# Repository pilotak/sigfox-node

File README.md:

# Sigfox temperature & humidity sensor

Outdoor battery powered temperature & humidity IOT sensor with integrated Sigfox transceiver and battery state monitor.

All data are sent to Sigfox backend, in order to save them to ie.: InfluxDB you can use  [Sigfox to InfluxDB convertor](https://github.com/pilotak/docker-sigfox-influxdb).

For more information please visit [wiki](./wiki)

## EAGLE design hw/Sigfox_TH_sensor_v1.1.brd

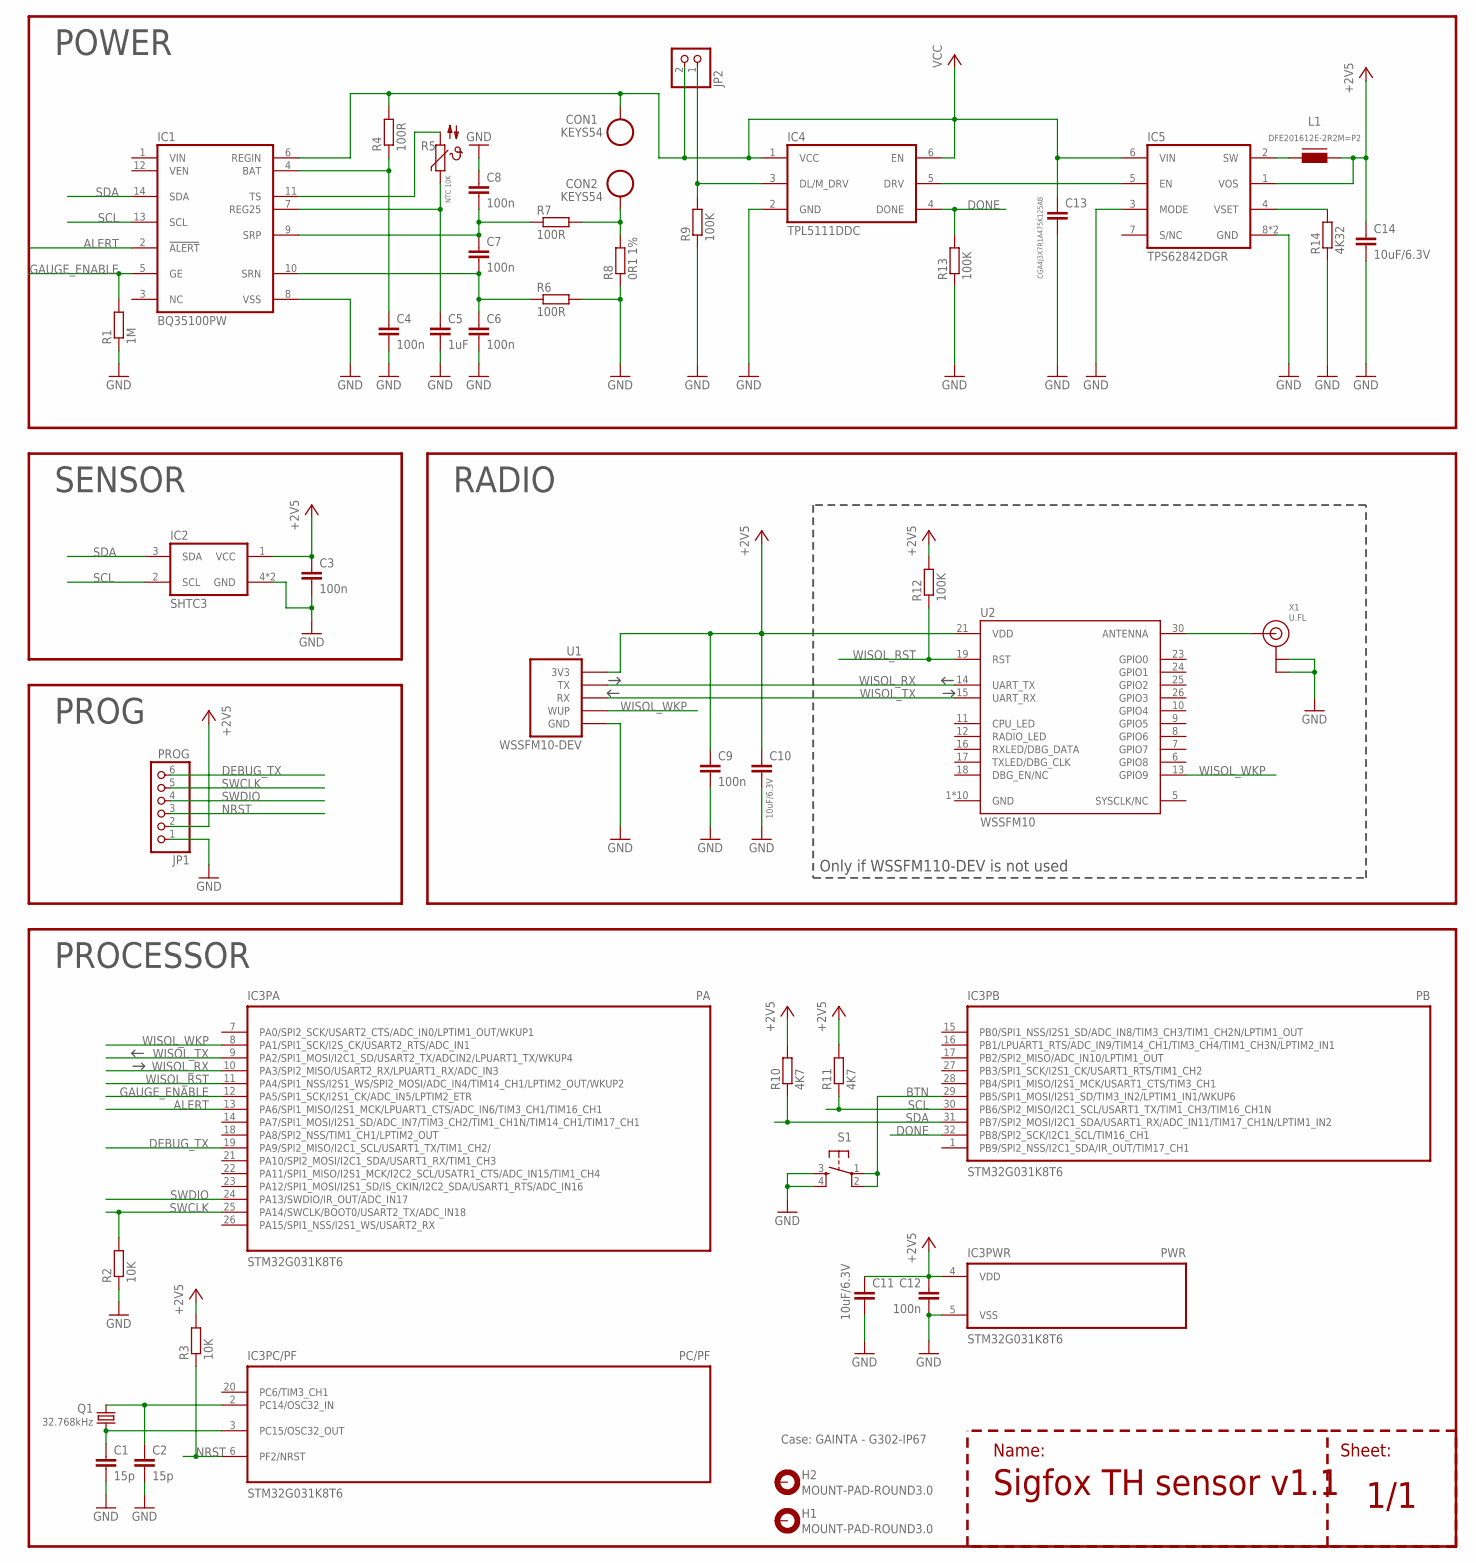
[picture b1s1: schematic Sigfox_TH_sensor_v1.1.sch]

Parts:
C1, C2: 15p; C0805
C3, C4, C6, C7, C8, C9, C12: 100n; C0805
C5: 1uF; C0805
C10, C11, C14: 10uF/6.3V; C0805
C13: CGA4J3X7R1A475K125AB; C0805
CON1, CON2: KEYS54
H1, H2: MOUNT-PAD-ROUND3.0; 3,0-PAD
IC1: BQ35100PW; TSSOP14
IC2: SHTC3; SON100P200X200X75-5T70X160N
IC3: STM32G031K8T6; TQFP32-08
IC4: TPL5111DDC; SOT23-6
IC5: TPS62842DGR; GHI-IC_MSOP-POWER.PAD-8(TI)
JP1: PROG; 1X06-S
JP2: PINHD-1X02_2.00; 1X02M
L1: DFE201612E-2R2M=P2; 0806
Q1: 32.768kHz; MM20SS
R1: 1M; R0805
R2, R3: 10K; R0805
R4, R6, R7: 100R; R0805
R5: NTC 10K; NTCM-HP
R8: 0R1 1%; R1206
R9, R12, R13: 100K; R0805
R10, R11: 4K7; R0805
R14: 4K32; R0805
S1: TACT_SWITCH-6X6X10-PTH; TACTILE-6X6-PTH
U1: WSSFM10-DEV
U2: WSSFM10
X1: U.FL

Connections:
+2V5: C3.1, C9.1, C10.1, C11.1, C12.1, C14.1, IC2.1 (VCC), IC3.4 (VDD), IC5.1 (VOS), JP1.2, L1.1, R3.2, R10.2, R11.2, R12.2, U1.3V3, U2.21 (VDD)
ALERT: IC1.2 (!ALERT!), IC3.13 (PA6/SPI1_MISO/I2S1_MCK/LPUART1_CTS/ADC_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)
BQ_2V5: C5.1, IC1.7 (REG25), R5.1
BTN: IC3.29 (PB5/SPI1_MOSI/I2S1_SD/TIM3_IN2/LPTIM1_I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), S1.1, S1.2
DEBUG_TX: IC3.19 (PA9/SPI2_MISO/I2C1_SCL/USART1_TX/TIM1_C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), JP1.6
DONE: IC3.32 (PB8/SPI2_SCK/I2C1_SCL/TIM16_CH1), IC4.4 (DONE), R13.2
GAUGE_ENABLE: IC1.5 (GE), IC3.12 (PA5/SPI1_SCK/I2S1_CK/ADC_IN5/LPTIM2_ETR), R1.2
GND: C1.2, C2.2, C3.2, C4.2, C5.2, C6.2, C8.1, C9.2, C10.2, C11.2, C12.2, C13.2, C14.2, IC1.8 (VSS), IC2.4 (GND), IC2.5 (GND), IC3.5 (VSS), IC4.2 (GND), IC5.3 (MODE), IC5.8 (GND), IC5.9 (GND), JP1.1, R1.1, R2.1, R6.2, R8.1, R9.1, R13.1, R14.1, S1.3, S1.4, U1.GND, U2.1 (GND), U2.2 (GND), U2.3 (GND), U2.4 (GND), U2.20 (GND), U2.22 (GND), U2.27 (GND), U2.28 (GND), U2.29 (GND), U2.31 (GND), X1.1 (GND), X1.2 (GND)
unnamed: IC5.4 (VSET), R14.2
unnamed: IC4.3 (DL/M_DRV), JP2.1, R9.2
unnamed: IC5.2 (SW), L1.2
unnamed: U2.30 (ANTENNA), X1.3 (SIGNAL)
unnamed: C1.1, IC3.3 (PC15/OSC32_OUT), Q1.4 (2)
unnamed: IC4.5 (DRV), IC5.5 (EN)
unnamed: C7.1, C8.2, IC1.9 (SRP), R7.1
unnamed: C6.1, C7.2, IC1.10 (SRN), R6.1
unnamed: C2.1, IC3.2 (PC14/OSC32_IN), Q1.1
unnamed: IC1.11 (TS), R5.2
unnamed: C4.1, IC1.4 (BAT), R4.1
NRST: IC3.6 (PF2/NRST), JP1.3, R3.1
PACK+: C13.1, CON1.1@0, CON1.1@1, CON1.1@2, IC1.6 (REGIN), IC4.1 (VCC), IC4.6 (EN), IC5.6 (VIN), JP2.2, R4.2
PACK-: CON2.1@0, CON2.1@1, CON2.1@2, R7.2, R8.2
SCL: IC1.13 (SCL), IC2.2 (SCL), IC3.30 (PB6/SPI2_MISO/I2C1_SCL/USART1_TX/TIM1_C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), R11.1
SDA: IC1.14 (SDA), IC2.3 (SDA), IC3.31 (PB7/SPI2_MOSI/I2C1_SDA/USART1_RX/ADC_IN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), R10.1
SWCLK: IC3.25 (PA14/SWCLK/BOOT0/USART2_TX/ADC_IN18), JP1.5, R2.2
SWDIO: IC3.24 (PA13/SWDIO/IR_OUT/ADC_IN17), JP1.4
WISOL_RST: IC3.11 (PA4/SPI1_NSS/I2S1_WS/SPI2_MOSI/ADC_IN4/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), R12.1, U2.19 (RST)
WISOL_RX: IC3.10 (PA3/SPI2_MISO/USART2_RX/LPUART1_RX/ADC_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), U1.TX, U2.14 (UART_TX)
WISOL_TX: IC3.9 (PA2/SPI1_MOSI/I2C1_SD/USART2_TX/ADCIN2/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), U1.RX, U2.15 (UART_RX)
WISOL_WKP: IC3.8 (PA1/SPI1_SCK/I2S_CK/USART2_RTS/ADC_IN1), U1.WUP, U2.13 (GPIO9)

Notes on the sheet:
Case: GAINTA - G302-IP67
POWER
Sigfox TH sensor v1.1
Sheet:
Name:
SENSOR
RADIO
Only if WSSFM110-DEV is not used
PROG
PROCESSOR

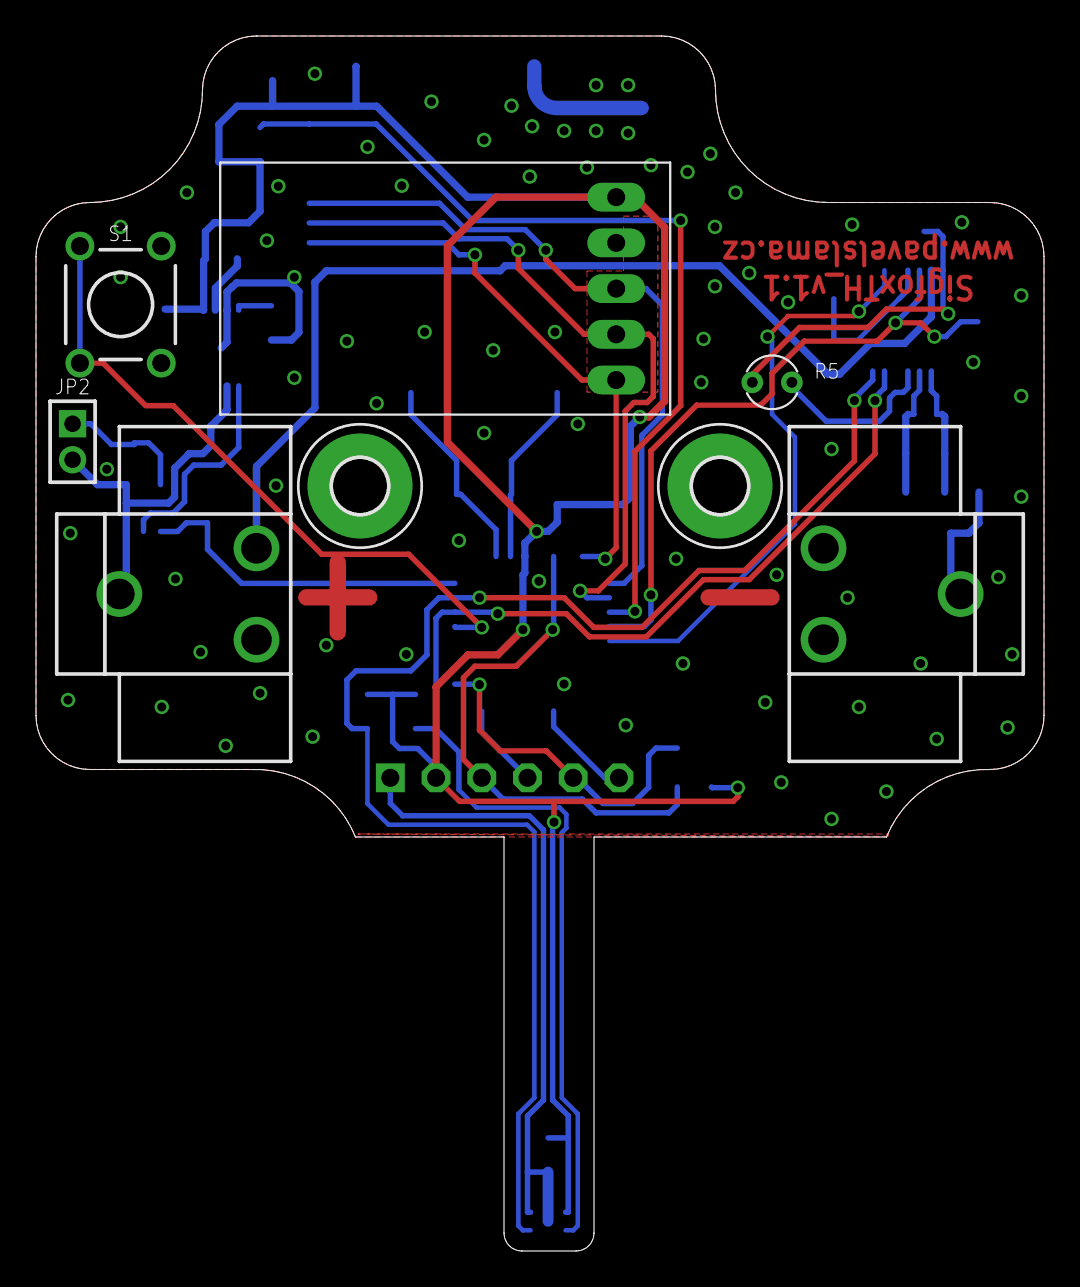
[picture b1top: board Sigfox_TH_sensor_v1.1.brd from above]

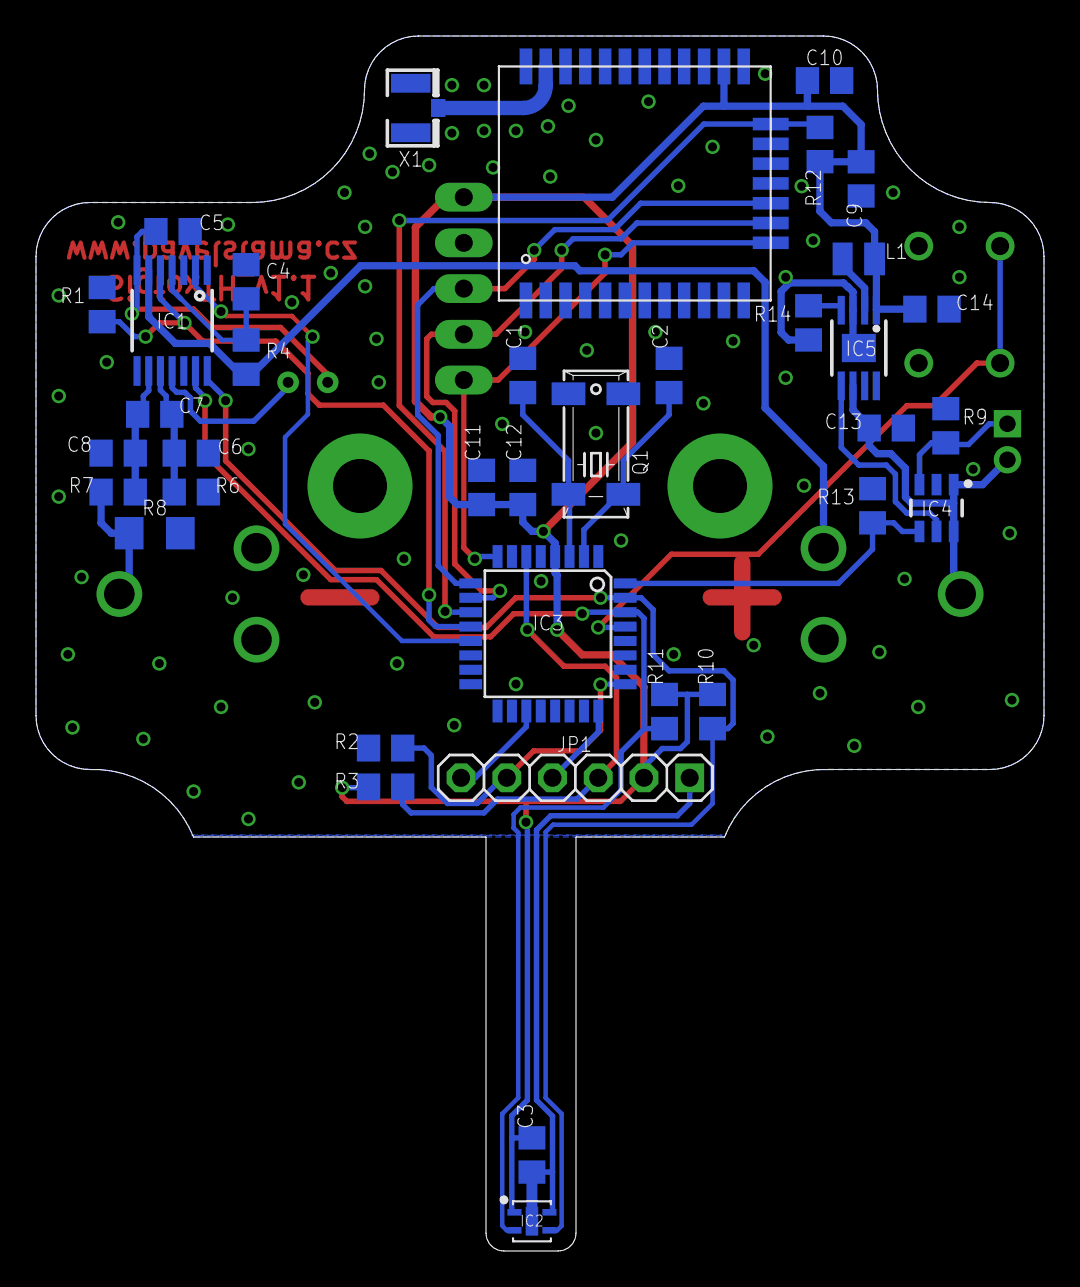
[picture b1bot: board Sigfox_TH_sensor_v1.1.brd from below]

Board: 2 copper layers, 56.0 x 67.5 mm, 46 parts (37 on the bottom side), 30 nets.

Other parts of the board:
CONN: SMA-PIGTAIL

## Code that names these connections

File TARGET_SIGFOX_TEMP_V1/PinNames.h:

/* mbed Microcontroller Library
 * SPDX-License-Identifier: BSD-3-Clause
 ******************************************************************************
 *
 * Copyright (c) 2018 STMicroelectronics.
 * All rights reserved.
 *
 * This software component is licensed by ST under BSD 3-Clause license,
 * the "License"; You may not use this file except in compliance with the
 * License. You may obtain a copy of the License at:
 *                        opensource.org/licenses/BSD-3-Clause
 *
 ******************************************************************************
 */

#ifndef MBED_PINNAMES_H
#define MBED_PINNAMES_H

#include "cmsis.h"
#include "PinNamesTypes.h"

#ifdef __cplusplus
extern "C" {
#endif

typedef enum {
    ALT0  = 0x100,
    ALT1  = 0x200,
    ALT2  = 0x300,
    ALT3  = 0x400
} ALTx;

typedef enum {
    PA_0  = 0x00,
    PA_1  = 0x01,
    PA_1_ALT0 = PA_1 | ALT0,
    PA_2  = 0x02,
    PA_2_ALT0 = PA_2 | ALT0,
    PA_2_ALT1 = PA_2 | ALT1,
    PA_3  = 0x03,
    PA_3_ALT0 = PA_3 | ALT0,
    PA_3_ALT1 = PA_3 | ALT1,
    PA_4  = 0x04,
    PA_5  = 0x05,
    PA_6  = 0x06,
    PA_6_ALT0 = PA_6 | ALT0,
    PA_7  = 0x07,
    PA_7_ALT0 = PA_7 | ALT0,
    PA_7_ALT1 = PA_7 | ALT1,
    PA_7_ALT2 = PA_7 | ALT2,
    PA_8  = 0x08,
    PA_9  = 0x09,
    PA_9_ALT0 = PA_9 | ALT0,
    PA_10 = 0x0A,
    PA_10_ALT0 = PA_10 | ALT0,
    PA_11 = 0x0B,
    PA_12 = 0x0C,
    PA_13 = 0x0D,
    PA_14 = 0x0E,
    PA_14_ALT0 = PA_14 | ALT0,
    PA_15 = 0x0F,
    PA_15_ALT0 = PA_15 | ALT0,

    PB_0  = 0x10,
    PB_0_ALT0 = PB_0 | ALT0,
    PB_1  = 0x11,
    PB_1_ALT0 = PB_1 | ALT0,
    PB_1_ALT1 = PB_1 | ALT1,
    PB_2  = 0x12,
    PB_3  = 0x13,
    PB_4  = 0x14,
    PB_4_ALT0 = PB_4 | ALT0,
    PB_4_ALT1 = PB_4 | ALT1,
    PB_5  = 0x15,
    PB_5_ALT0 = PB_5 | ALT0,
    PB_5_ALT1 = PB_5 | ALT1,
    PB_6  = 0x16,
    PB_6_ALT0 = PB_6 | ALT0,
    PB_7  = 0x17,
    PB_8  = 0x18,
    PB_9  = 0x19,
    PB_10 = 0x1A,
    PB_11 = 0x1B,
    PB_12 = 0x1C,
    PB_13 = 0x1D,
    PB_13_ALT0 = PB_13 | ALT0,
    PB_14 = 0x1E,
    PB_14_ALT0 = PB_14 | ALT0,
    PB_15 = 0x1F,
    PB_15_ALT0 = PB_15 | ALT0,
    PB_15_ALT1 = PB_15 | ALT1,

    PC_0  = 0x20,
    PC_1  = 0x21,
    PC_2  = 0x22,
    PC_3  = 0x23,
    PC_4  = 0x24,
    PC_4_ALT0 = PC_4 | ALT0,
    PC_5  = 0x25,
    PC_5_ALT0 = PC_5 | ALT0,
    PC_6  = 0x26,
    PC_6_ALT0 = PC_6 | ALT0,
    PC_7  = 0x27,
    PC_7_ALT0 = PC_7 | ALT0,
    PC_8  = 0x28,
    PC_8_ALT0 = PC_8 | ALT0,
    PC_9  = 0x29,
    PC_9_ALT0 = PC_9 | ALT0,
    PC_10 = 0x2A,
    PC_10_ALT0 = PC_10 | ALT0,
    PC_11 = 0x2B,
    PC_11_ALT0 = PC_11 | ALT0,
    PC_12 = 0x2C,
    PC_13 = 0x2D,
    PC_14 = 0x2E,
    PC_15 = 0x2F,

    PD_0  = 0x30,
    PD_1  = 0x31,
    PD_2  = 0x32,
    PD_3  = 0x33,
    PD_4  = 0x34,
    PD_5  = 0x35,
    PD_6  = 0x36,
    PD_8  = 0x38,
    PD_9  = 0x39,

    PF_0  = 0x50,
    PF_1  = 0x51,

    // ADC internal channels
    ADC_TEMP = 0xF0,
    ADC_VREF = 0xF1,
    ADC_VBAT = 0xF2,

    // STDIO for console print
    STDIO_UART_TX = PA_9,
    STDIO_UART_RX = PA_10,

    USER_BUTTON = PB_5,

    WISOL_TX = PA_2_ALT0, // LowPower UART
    WISOL_RX = PA_3_ALT0,
    WISOL_RST_PIN = PA_4,
    WISOL_WKP_PIN = PA_1,

    GAUGE_ENABLE_PIN = PA_5,
    DONE_PIN = PB_8,

    // Standardized button names
    LED1 = PB_8,
    BUTTON1     = USER_BUTTON,
    SERIAL_TX   = STDIO_UART_TX,
    SERIAL_RX   = STDIO_UART_RX,
    USBTX       = STDIO_UART_TX,
    USBRX       = STDIO_UART_RX,
    I2C_SCL     = PB_6,
    I2C_SDA     = PB_7,
    SPI_MOSI    = PA_7,
    SPI_MISO    = PA_6,
    SPI_SCK     = PA_5,
    SPI_CS      = PB_0,
    PWM_OUT     = PB_3,

    /**** OSCILLATOR pins ****/
    RCC_OSC32_EN = PC_15,
    RCC_OSC32_IN = PC_14,
    RCC_OSC32_OUT = PC_15,
    RCC_OSC_EN = PC_15,
    RCC_OSC_IN = PC_14,

    /**** DEBUG pins ****/
    SYS_PVD_IN = PB_7,
    SYS_SWCLK = PA_14,
    SYS_SWDIO = PA_13,
    SYS_WKUP1 = PA_0,
    SYS_WKUP2 = PA_4,
    SYS_WKUP4 = PA_2,
    SYS_WKUP6 = PB_5,

    // Not connected
    NC = (int)0xFFFFFFFF
} PinName;

#ifdef __cplusplus
}
#endif

#endif

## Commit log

2020-09-14 init
2020-10-07 general update
2020-11-04 debug update
2020-11-04 update deps + calibration example
2020-11-04 CI build
2020-11-04 calibration examples + lib update
2020-11-04 CI install ARM GCC 9-2019q4
2020-11-04 CI update ARM GCC install
2020-11-04 CI remove mercurial & update gcc path
2020-11-04 CI yet another GCC PATH update
2020-11-04 CI sudo access
2020-11-05 more examples & lib update
2020-11-05 readme update
2020-11-08 use 0.4bit gain for temperature & humidity
2020-11-08 update libs
2020-11-08 target pins enable LPUART
2020-11-08 CI release
2020-11-08 CI mkdir fix
2020-11-08 CI fix FW location
2020-11-08 CI update file location
2020-11-08 CI release new filenames
2020-11-11 folder restructure + images
2020-11-11 CO path update
2020-11-11 CI path update
2020-11-11 Ci change to working-directory setting
2020-11-11 CI global working-dir update
2020-11-11 update images
2021-05-29 docu
2021-05-29 fix build
2021-07-06 OSHW logo
